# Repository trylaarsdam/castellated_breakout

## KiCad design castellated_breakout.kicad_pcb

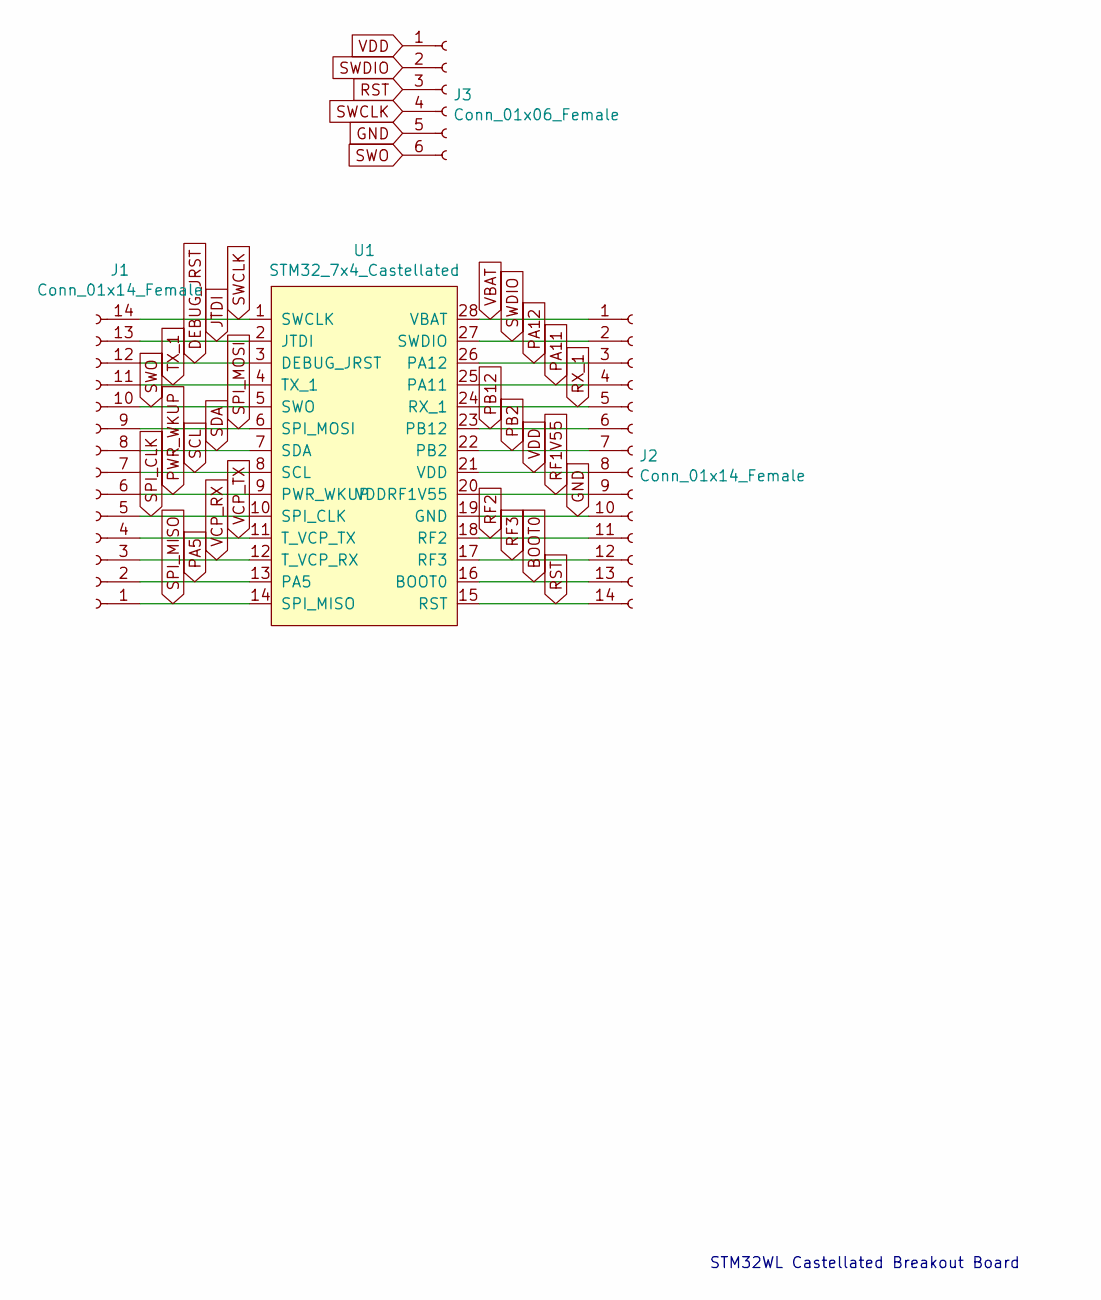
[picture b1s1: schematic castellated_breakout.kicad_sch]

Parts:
J1, J2: Conn_01x14_Female; PinSocket_1x14_P2.54mm_Vertical
J3: Conn_01x06_Female; Tag-Connect_TC2030-IDC-FP_2x03_P1.27mm_Vertical
U1: STM32_7x4_Castellated; 7x4_Castellated

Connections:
BOOT0: J2.13, U1.16 (BOOT0)
DEBUG_JRST: J1.12, U1.3 (DEBUG_JRST)
GND: J2.10, J3.5, U1.19 (GND)
JTDI: J1.13, U1.2 (JTDI)
PA5: J1.2, U1.13 (PA5)
PA11: J2.4, U1.25 (PA11)
PA12: J2.3, U1.26 (PA12)
PB2: J2.7, U1.22 (PB2)
PB12: J2.6, U1.23 (PB12)
PWR_WKUP: J1.6, U1.9 (PWR_WKUP)
RF1V55: J2.9, U1.20 (VDDRF1V55)
RF2: J2.11, U1.18 (RF2)
RF3: J2.12, U1.17 (RF3)
RST: J2.14, J3.3, U1.15 (RST)
RX_1: J2.5, U1.24 (RX_1)
SCL: J1.7, U1.8 (SCL)
SDA: J1.8, U1.7 (SDA)
SPI_CLK: J1.5, U1.10 (SPI_CLK)
SPI_MISO: J1.1, U1.14 (SPI_MISO)
SPI_MOSI: J1.9, U1.6 (SPI_MOSI)
SWCLK: J1.14, J3.4, U1.1 (SWCLK)
SWDIO: J2.2, J3.2, U1.27 (SWDIO)
SWO: J1.10, J3.6, U1.5 (SWO)
TX_1: J1.11, U1.4 (TX_1)
VBAT: J2.1, U1.28 (VBAT)
VCP_RX: J1.3, U1.12 (T_VCP_RX)
VCP_TX: J1.4, U1.11 (T_VCP_TX)
VDD: J2.8, J3.1, U1.21 (VDD)

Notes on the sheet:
STM32WL Castellated Breakout Board

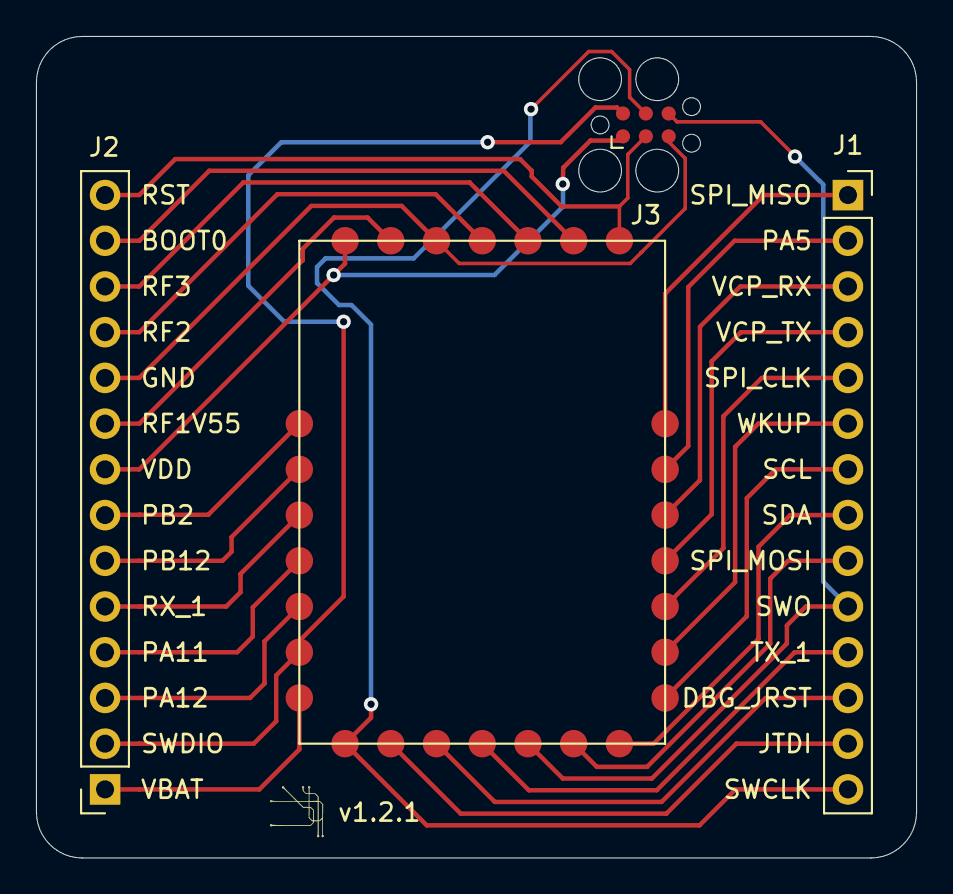
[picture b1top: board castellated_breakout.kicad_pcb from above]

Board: 2 copper layers, 48.9 x 45.6 mm, 4 parts (0 on the bottom side), 28 nets.

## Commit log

2021-07-27 init
2021-07-27 castellated board lib
2021-07-27 schematic
2021-07-27 board layout + route
2021-07-27 spaced out traces
2021-07-27 gerbers, v1
2021-07-28 v2 voltera, v1 pcbway
2021-08-04 v2 pcbway
2022-01-05 locking tag connect
2022-01-05 gerbers not in x2
